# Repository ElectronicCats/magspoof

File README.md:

# MagSpoof By Electronic Cats
  
<a href="https://github.com/ElectronicCats/magspoof/wiki">

<p align=center>

</p>

<p align=center>
Also available at distributors:
</p>
<p align=center>

</p>

# What is MagSpoof?

**MagSpoof by Electronic Cats** is a device that can spoof/emulate any magnetic stripe or credit card. It can work "wirelessly", even on **standard magstripe/credit card readers**, by generating a strong electromagnetic field that emulates a traditional magnetic stripe card.

* Allows you to store all of your credit cards and magstripes in one device
* Works on traditional magstripe readers **wirelessly** (no NFC/RFID required)
* Can **disable** Chip-and-PIN (code not included)
* Correctly **predicts** Amex credit card numbers + expirations from previous card number (code not included)
* Supports all three magnetic stripe tracks, and even supports Track 1+2 simultaneously
* Easy to build using Arduino or other common parts

MagSpoof can be used as a traditional credit card and simply store all of your credit cards (and with modification, can technically disable chip requirements) in various impressive and exciting form factors, or can be used for security research in any area that would traditionally require a magstripe, such as readers for credit cards, drivers licenses, hotel room keys, automated parking lot tickets, etc.

**Note**: The Chip-and-PIN and Amex information is **not** implemented and using MagSpoof requires you to have/own the magstripes that you wish to emulate. Simply having a credit card number and expiration is not enough to perform transactions. MagSpoof **does** allow you to perform research in other areas of magstripes, microcontrollers, and electromagnetism, as well as learn about and create your own devices similar to other existing, commercial technologies such as <a href="http://www.samsung.com/us/support/answer/ANS00043865/997410383/">Samsung MST</a> and <a href="https://onlycoin.com/">Coin</a>.</p>

### ⚠️ Disclaimer ⚠️
MagSpoof is a wireless penetration testing tool intended solely for use in authorized security audits, where such usage is permitted by applicable laws and regulations. Before utilizing this tool, it is crucial to ensure compliance with all relevant legal requirements and obtain appropriate permissions from the relevant authorities.

It is essential to notice that the board does not provide any means or authorization to utilize credit cards or engage in any financial transactions that are not legally authorized. Electronic Cats holds no responsibility for any unauthorized use of the tool or any resulting damages.

-----

# Based in work of Samy Kamkar

**Point of Contact:** [@SamyKamkar](https://twitter.com/samykamkar)

You can see more of my projects at <http://samy.pl> or contact me at <code@samy.pl>.

------

## How to contribute 
 Contributions are welcome! 

Please read the document  [**Contribution Manual**](https://github.com/ElectronicCats/electroniccats-cla/blob/main/electroniccats-contribution-manual.md)  which will show you how to contribute your changes to the project.

✨ Thanks to all our [contributors](https://github.com/ElectronicCats/magspoof/graphs/contributors)! ✨

See  [**_Electronic Cats CLA_**](https://github.com/ElectronicCats/electroniccats-cla/blob/main/electroniccats-cla.md) for more information.

See the [**community code of conduct**](https://github.com/ElectronicCats/electroniccats-cla/blob/main/electroniccats-community-code-of-conduct.md)   for a vision of the community we want to build and what we expect from it.

### Maintainer

Electronic Cats invests time and resources in providing this open-source design design, please support Electronic Cats and open-source hardware by purchasing products from Electronic Cats!

# License

Electronic Cats invests time and resources in providing this open-source design. Please support Electronic Cats and open-source hardware by purchasing products from Electronic Cats!

Designed by Electronic Cats.

Firmware released under an GNU AGPL v3.0 license. See the LICENSE file for more information.

Hardware released under an CERN Open Hardware Licence v1.2. See the LICENSE_HARDWARE file for more information.

Electronic Cats is a registered trademark, please do not use if you sell these PCBs.

30 Octuber 2019

------

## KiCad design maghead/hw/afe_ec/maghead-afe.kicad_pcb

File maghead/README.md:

# MagHead · cabezal lector de banda magnética integrado en PCB (experimento rev A)

Trabajo de investigación y primer experimento fabricable para un sucesor del MagSpoof V5 con lectura y emulación integradas. **Nada de lo que hay aquí se ha construido ni medido todavía**: son cálculos, simulación ideal, diseños de PCB verificados por DRC y software probado con señales sintéticas.

## Recomendación

1. **Ruta principal: cabezal híbrido plano.** Bobinas impresas en la PCB (no en la capa que toca la tarjeta) alrededor de dos ranuras, y una cinta de material magnético blando de 18–50 µm que pasa por las ranuras y forma polos y entrehierro sobre la cara de la PCB. El análisis muestra que dos láminas delgadas coplanares leen igual que un cabezal de anillo del mismo entrehierro; el núcleo no necesita altura. Añade ~0.1 mm al espesor de la placa.
2. **La bobina impresa sin núcleo no sirve como lector de pista 1** (la pista mínima de PCB ya es más ancha que la separación entre transiciones, y equivale a media espira), **pero sí se fabrica como instrumento**: mide el flujo absoluto de la banda y la pérdida por separación, que son las incógnitas que hoy dejan la señal del híbrido con un factor 3 de incertidumbre.
3. **Magnetorresistivos: no en esta tanda.** No hay ningún sensor con distribución establecida cuya geometría esté verificada para 210 bpi; los candidatos solo son plausibles para pista 2 y faltan dos datos del fabricante.
4. **Primero pista 2, después pista 1 con el mismo cabezal** (el cupón se recoloca 3.30 mm con pasadores). Pista 2 valida la cadena; pista 1 decide si la geometría sirve.
5. El riesgo dominante no es el entrehierro ni el ruido, sino **mantener la banda a ≤ 25 µm del polo** con una superficie plana: en pista 1 cada micrómetro cuesta 0.45 dB.

Objetivo mecánico que sale de simular el decodificador: PW50 ≤ ~100 µm en pista 1, es decir separación banda–polo ≲ 35 µm con entrehierro a tope de 25 µm y ≲ 15–20 µm con el de solape.

Números clave (estimaciones, ver `docs/01`): señal del cupón H ≈ 45–250 µV de pico a 19 cm/s (15–50 veces menos que un cabezal comercial), fuente de ≈ 12 Ω, SNR estimada ≥ 26 dB en el peor caso con el frente analógico propuesto.

## Qué se propone fabricar

| Pieza | Qué es |
|---|---|
| `hw/coupon_H` | Cupón híbrido, 4 capas 0.8 mm: 2 sitios × (2 bobinas de 36 espiras en serie-oposición + 2 ranuras). Cinco variantes de ensamblaje sobre la misma PCB |
| `hw/coupon_A` | Cupón de pistas al aire, 2 capas: 3 pistas simples + 1 meandro adaptado a pista 2 |
| `hw/fixture` | Base con lengüetas de presión fresadas y compuertas ópticas, y separador/guía de 1.0 mm. Con el cupón forman el "sándwich" de 2.8 mm |
| `hw/afe` | Frente analógico de 2 canales: esquemático y PCB de 90 × 60 mm, 4 capas |

## Mapa del repositorio

| Ruta | Contenido |
|---|---|
| `docs/01_investigacion_y_calculos.md` | MagSpoof V5 verificado, ISO 7811, física, resultados del modelo, comparación de arquitecturas, fuentes |
| `docs/02_cupones_y_ensamblaje.md` | Geometría, stackup, variantes, procedimiento de ensamblaje, tolerancias, presupuesto de espesor |
| `docs/03_frente_analogico_y_adquisicion.md` | AFE, elección ADC/comparador, placa de desarrollo |
| `docs/04_plan_de_pruebas.md` | Instrumentación, pruebas T0–T10, métricas L1/L2/L3, puertas de decisión |
| `docs/05_incertidumbres_y_pendientes.md` | Parámetros desconocidos, estado de cada entregable, excepciones de DRC, lista previa al pedido |
| `docs/BOM.md` | Fabricantes, números de parte y canales |
| `calc/head_model.py`, `calc/out/` | Modelo: sensibilidad 2D, formas de onda F2F, eficiencia, amplitudes |
| `drawings/` | Secciones y detalle del entrehierro acotados (SVG + PNG, generados por script) |
| `hw/gen_pcbs.py`, `hw/build.sh` | Generador paramétrico de las PCBs, DRC y exportación |
| `hw/*/fab_*`, `hw/*/*_revA_gerbers.zip` | Gerbers y taladros **candidatos**, no liberados |
| `fw/` | Firmware de captura para Pico 2 y decodificador F2F portable en C |
| `tools/` | Síntesis de señal, decodificación, captura, métricas e informes en Python |

## Verificaciones hechas

- KiCad 9.0.9: DRC de las cuatro tarjetas con 0 errores y 0 conexiones pendientes; ERC del AFE con 0 errores y 0 advertencias; PCB del AFE con DRC y paridad de esquemático en 0 errores.
- Comprobación geométrica propia de separación entre espiras (el DRC no la cubre al ser una sola red): mínimo 0.127 mm, 0 violaciones.
- Netlist del AFE contra tabla independiente: coincide.
- Software: 172 pruebas en Python y 125 comprobaciones en C superadas con señales sintéticas; el firmware compila para Pico 2 y Pico con el SDK real, sin probar en placa.
- Solver de campo contra la solución analítica de Karlqvist: 1.5 % en el pico.

## Qué falta para fabricar

La lista completa está en `docs/05`, §4. Lo esencial: revisión humana de los diseños, confirmar capacidades del fabricante de PCB (ranuras de 1.0 mm, 0.127 mm en 4 capas de 0.8 mm), verificar la huella del sensor óptico contra su hoja de datos, tener el material magnético confirmado y elegir el cabezal comercial de referencia.

## Reproducir

```sh
pip install numpy scipy matplotlib cairosvg
python3 calc/head_model.py          # modelo y figuras
python3 drawings/make_drawings.py   # dibujos
sh hw/build.sh                      # PCBs + DRC + Gerbers (usa la imagen Docker kicad/kicad:9.0)
sh hw/afe/build.sh                  # esquemático + ERC + netlist
```

Licencia: la del repositorio (hardware abierto, ver `LICENSE_HARDWARE`).

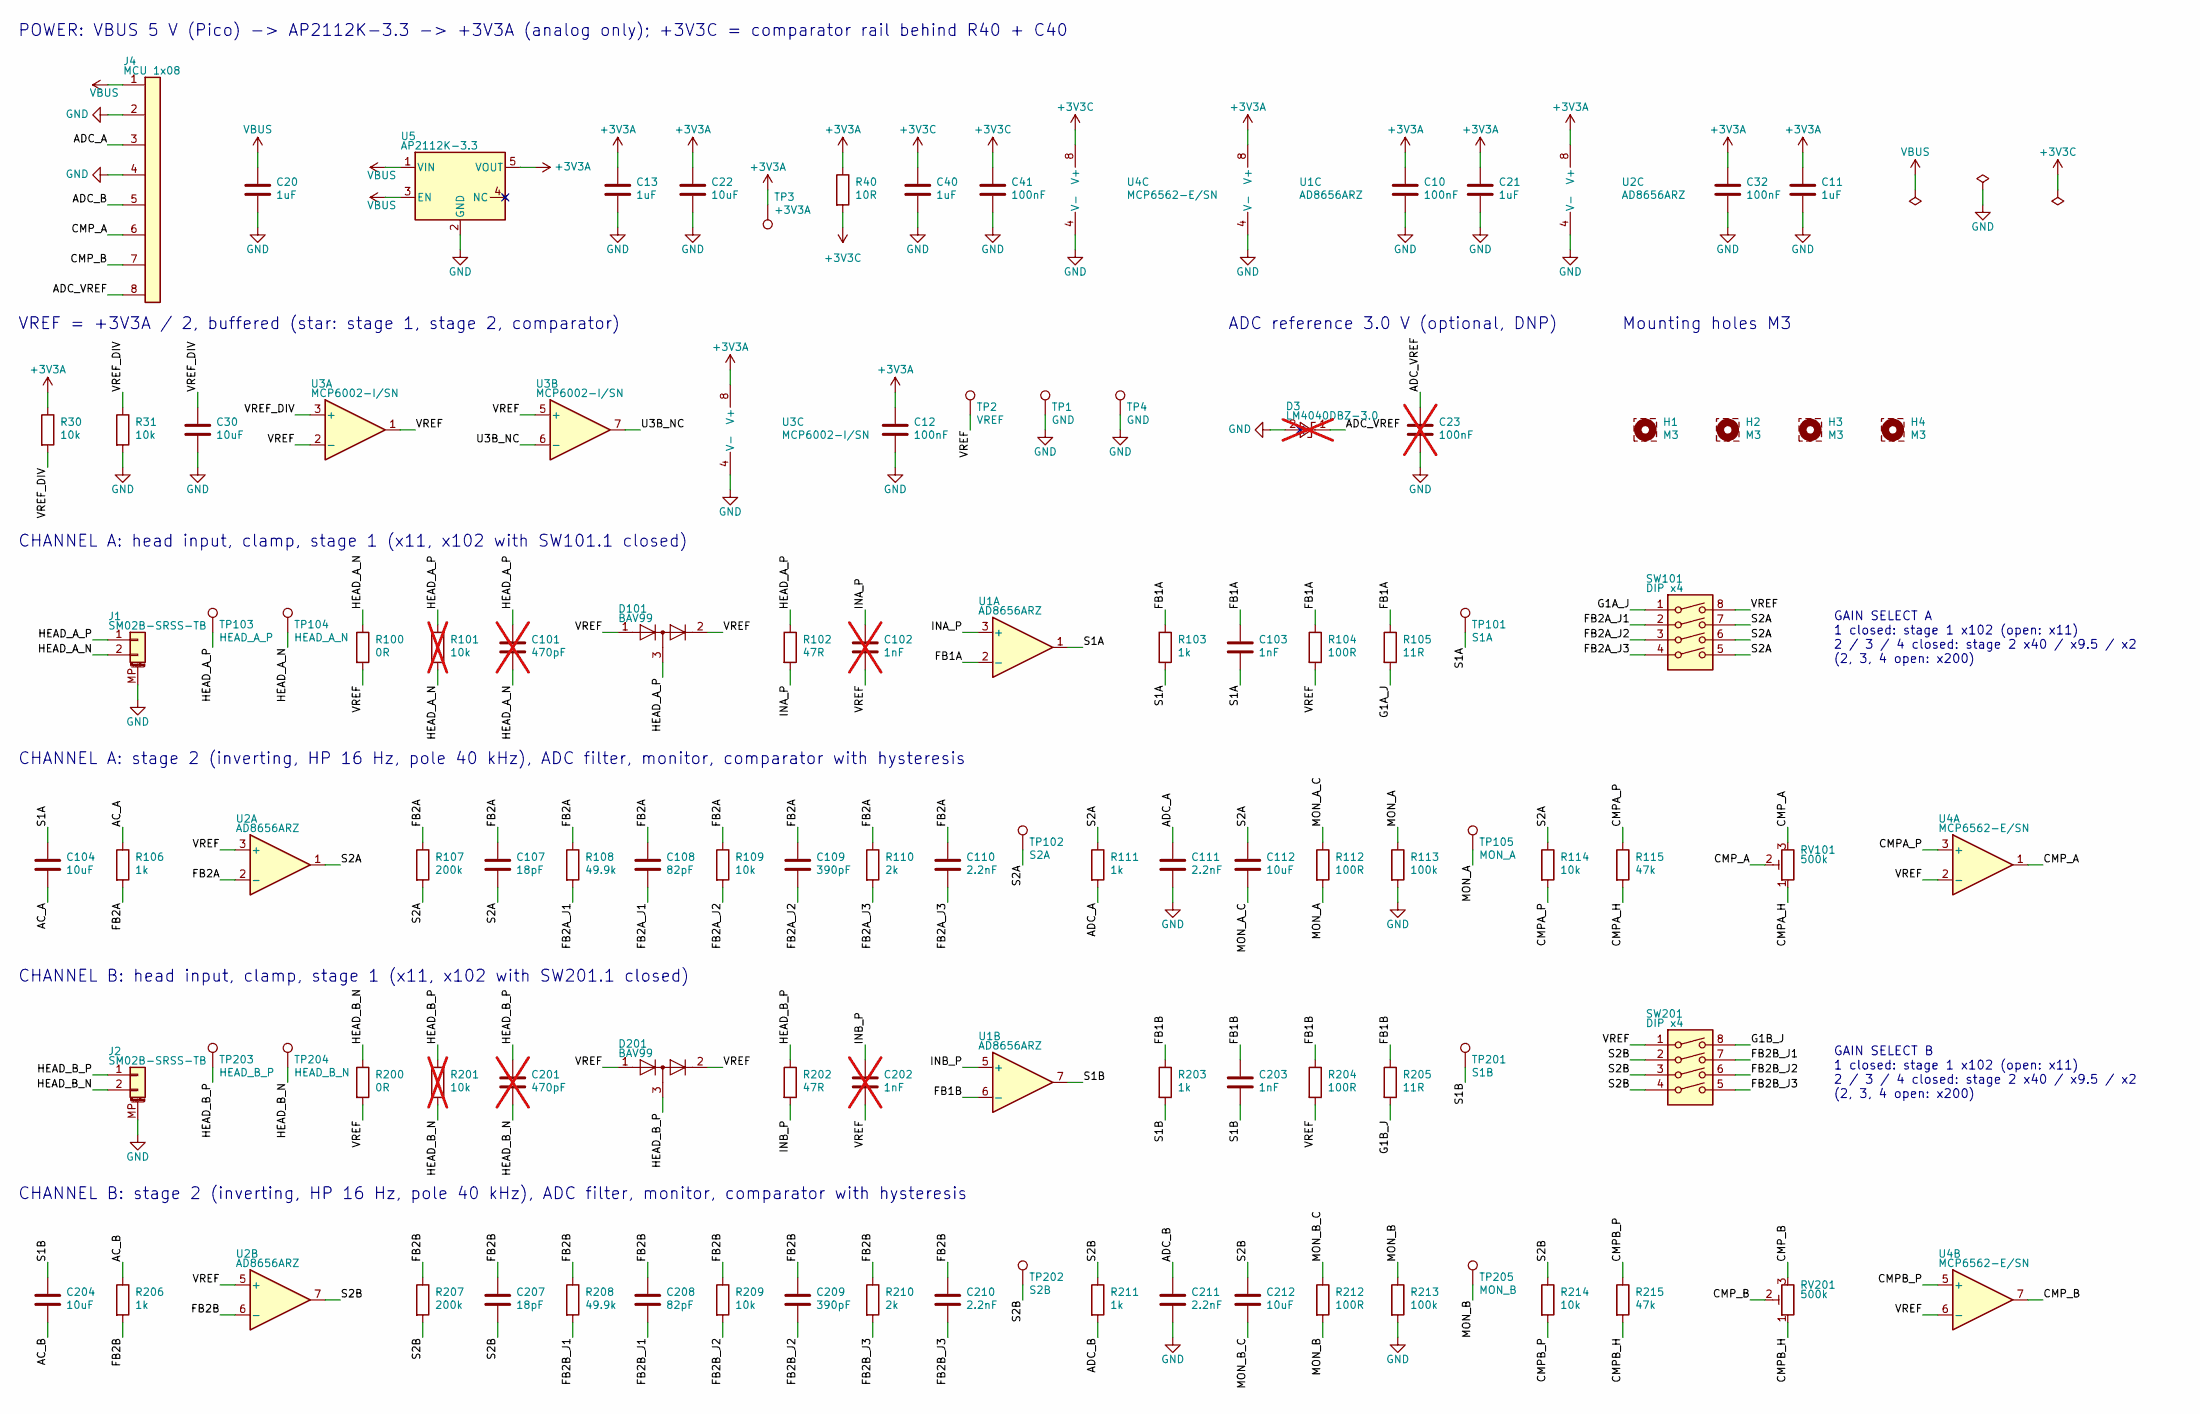
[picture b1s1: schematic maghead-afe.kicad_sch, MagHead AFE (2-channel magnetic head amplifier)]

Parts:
C10, C12, C32, C41: 100nF; C_0603_1608Metric
C11, C13, C20, C21, C40: 1uF; C_0603_1608Metric
C22, C30, C104, C112, C204, C212: 10uF; C_0603_1608Metric
C23: 100nF; C_0603_1608Metric; not fitted
C101, C201: 470pF; C_0603_1608Metric; not fitted
C102, C202: 1nF; C_0603_1608Metric; not fitted
C103, C203: 1nF; C_0603_1608Metric
C107, C207: 18pF; C_0603_1608Metric
C108, C208: 82pF; C_0603_1608Metric
C109, C209: 390pF; C_0603_1608Metric
C110, C111, C210, C211: 2.2nF; C_0603_1608Metric
D3: LM4040DBZ-3.0; SOT-23; not fitted
D101, D201: BAV99; SOT-23
H1, H2, H3, H4: M3; MountingHole_3.2mm_M3
J1, J2: SM02B-SRSS-TB; JST_SH_SM02B-SRSS-TB_1x02-1MP_P1.00mm_Horizontal
J4: MCU 1x08; PinHeader_1x08_P2.54mm_Vertical
R30, R31, R109, R114, R209, R214: 10k; R_0603_1608Metric
R40: 10R; R_0603_1608Metric
R100, R200: 0R; R_0603_1608Metric
R101, R201: 10k; R_0603_1608Metric; not fitted
R102, R202: 47R; R_0603_1608Metric
R103, R106, R111, R203, R206, R211: 1k; R_0603_1608Metric
R104, R112, R204, R212: 100R; R_0603_1608Metric
R105, R205: 11R; R_0603_1608Metric
R107, R207: 200k; R_0603_1608Metric
R108, R208: 49.9k; R_0603_1608Metric
R110, R210: 2k; R_0603_1608Metric
R113, R213: 100k; R_0603_1608Metric
R115, R215: 47k; R_0603_1608Metric
RV101, RV201: 500k; Potentiometer_Bourns_TC33X_Vertical
SW101, SW201: DIP x4; SW_DIP_SPSTx04_Slide_KingTek_DSHP04TS_W7.62mm_P1.27mm
TP1, TP4: GND; TestPoint_Pad_D1.5mm
TP2: VREF; TestPoint_Pad_D1.5mm
TP3: +3V3A; TestPoint_Pad_D1.5mm
TP101: S1A; TestPoint_Pad_D1.5mm
TP102: S2A; TestPoint_Pad_D1.5mm
TP103: HEAD_A_P; TestPoint_Pad_2.0x2.0mm
TP104: HEAD_A_N; TestPoint_Pad_2.0x2.0mm
TP105: MON_A; TestPoint_Pad_D1.5mm
TP201: S1B; TestPoint_Pad_D1.5mm
TP202: S2B; TestPoint_Pad_D1.5mm
TP203: HEAD_B_P; TestPoint_Pad_2.0x2.0mm
TP204: HEAD_B_N; TestPoint_Pad_2.0x2.0mm
TP205: MON_B; TestPoint_Pad_D1.5mm
U1, U2: AD8656ARZ; SOIC-8_3.9x4.9mm_P1.27mm
U3: MCP6002-I/SN; SOIC-8_3.9x4.9mm_P1.27mm
U4: MCP6562-E/SN; SOIC-8_3.9x4.9mm_P1.27mm
U5: AP2112K-3.3; SOT-23-5; LCSC# C47773

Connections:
+3V3A: C10.1, C11.1, C12.1, C13.1, C21.1, C22.1, C32.1, R30.1, R40.1, TP3.1, U1.8 (V+), U2.8 (V+), U3.8 (V+), U5.5 (VOUT)
+3V3C: C40.1, C41.1, R40.2, U4.8 (V+)
/AC_A: C104.2, R106.1
/AC_B: C204.2, R206.1
/ADC_A: C111.1, J4.3, R111.2
/ADC_B: C211.1, J4.5, R211.2
/ADC_VREF: C23.1, D3.1 (K), J4.8
/CMPA_H: R115.2, RV101.1
/CMPA_P: R114.2, R115.1, U4.3 (+)
/CMPB_H: R215.2, RV201.1
/CMPB_P: R214.2, R215.1, U4.5 (+)
/CMP_A: J4.6, RV101.2, RV101.3, U4.1
/CMP_B: J4.7, RV201.2, RV201.3, U4.7
/FB1A: C103.1, R103.1, R104.1, R105.1, U1.2 (-)
/FB1B: C203.1, R203.1, R204.1, R205.1, U1.6 (-)
/FB2A: C107.1, C108.1, C109.1, C110.1, R106.2, R107.1, R108.1, R109.1, R110.1, U2.2 (-)
/FB2A_J1: C108.2, R108.2, SW101.2
/FB2A_J2: C109.2, R109.2, SW101.3
/FB2A_J3: C110.2, R110.2, SW101.4
/FB2B: C207.1, C208.1, C209.1, C210.1, R206.2, R207.1, R208.1, R209.1, R210.1, U2.6 (-)
/FB2B_J1: C208.2, R208.2, SW201.7
/FB2B_J2: C209.2, R209.2, SW201.6
/FB2B_J3: C210.2, R210.2, SW201.5
/G1A_J: R105.2, SW101.1
/G1B_J: R205.2, SW201.8
/HEAD_A_N: C101.2, J1.2, R100.1, R101.2, TP104.1
/HEAD_A_P: C101.1, D101.3 (K), J1.1, R101.1, R102.1, TP103.1
/HEAD_B_N: C201.2, J2.2, R200.1, R201.2, TP204.1
/HEAD_B_P: C201.1, D201.3 (K), J2.1, R201.1, R202.1, TP203.1
/INA_P: C102.1, R102.2, U1.3 (+)
/INB_P: C202.1, R202.2, U1.5 (+)
/MON_A: R112.2, R113.1, TP105.1
/MON_A_C: C112.2, R112.1
/MON_B: R212.2, R213.1, TP205.1
/MON_B_C: C212.2, R212.1
/S1A: C103.2, C104.1, R103.2, TP101.1, U1.1
/S1B: C203.2, C204.1, R203.2, TP201.1, U1.7
/S2A: C107.2, C112.1, R107.2, R111.1, R114.1, SW101.5, SW101.6, SW101.7, TP102.1, U2.1
/S2B: C207.2, C212.1, R207.2, R211.1, R214.1, SW201.2, SW201.3, SW201.4, TP202.1, U2.7
/U3B_NC: U3.6 (-), U3.7
/VREF: C102.2, C202.2, D101.1 (K), D101.2 (A), D201.1 (K), D201.2 (A), R100.2, R104.2, R200.2, R204.2, SW101.8, SW201.1, TP2.1, U2.3 (+), U2.5 (+), U3.1, U3.2 (-), U3.5 (+), U4.2 (-), U4.6 (-)
/VREF_DIV: C30.1, R30.2, R31.1, U3.3 (+)
GND: C10.2, C11.2, C12.2, C13.2, C20.2, C21.2, C22.2, C23.2, C30.2, C32.2, C40.2, C41.2, C111.2, C211.2, D3.2 (A), J1.MP (MountPin), J2.MP (MountPin), J4.2, J4.4, R31.2, R113.2, R213.2, TP1.1, TP4.1, U1.4 (V-), U2.4 (V-), U3.4 (V-), U4.4 (V-), U5.2 (GND)
VBUS: C20.1, J4.1, U5.1 (VIN), U5.3 (EN)

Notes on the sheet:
POWER: VBUS 5 V (Pico) -> AP2112K-3.3 -> +3V3A (analog only); +3V3C = comparator rail behind R40 + C40
VREF = +3V3A / 2, buffered (star: stage 1, stage 2, comparator)
ADC reference 3.0 V (optional, DNP)
Mounting holes M3
CHANNEL A: head input, clamp, stage 1 (x11, x102 with SW101.1 closed)
GAIN SELECT A 1 closed: stage 1 x102 (open: x11) 2 / 3 / 4 closed: stage 2 x40 / x9.5 / x2 (2, 3, 4 open: x200)
CHANNEL A: stage 2 (inverting, HP 16 Hz, pole 40 kHz), ADC filter, monitor, comparator with hysteresis
CHANNEL B: head input, clamp, stage 1 (x11, x102 with SW201.1 closed)
GAIN SELECT B 1 closed: stage 1 x102 (open: x11) 2 / 3 / 4 closed: stage 2 x40 / x9.5 / x2 (2, 3, 4 open: x200)
CHANNEL B: stage 2 (inverting, HP 16 Hz, pole 40 kHz), ADC filter, monitor, comparator with hysteresis

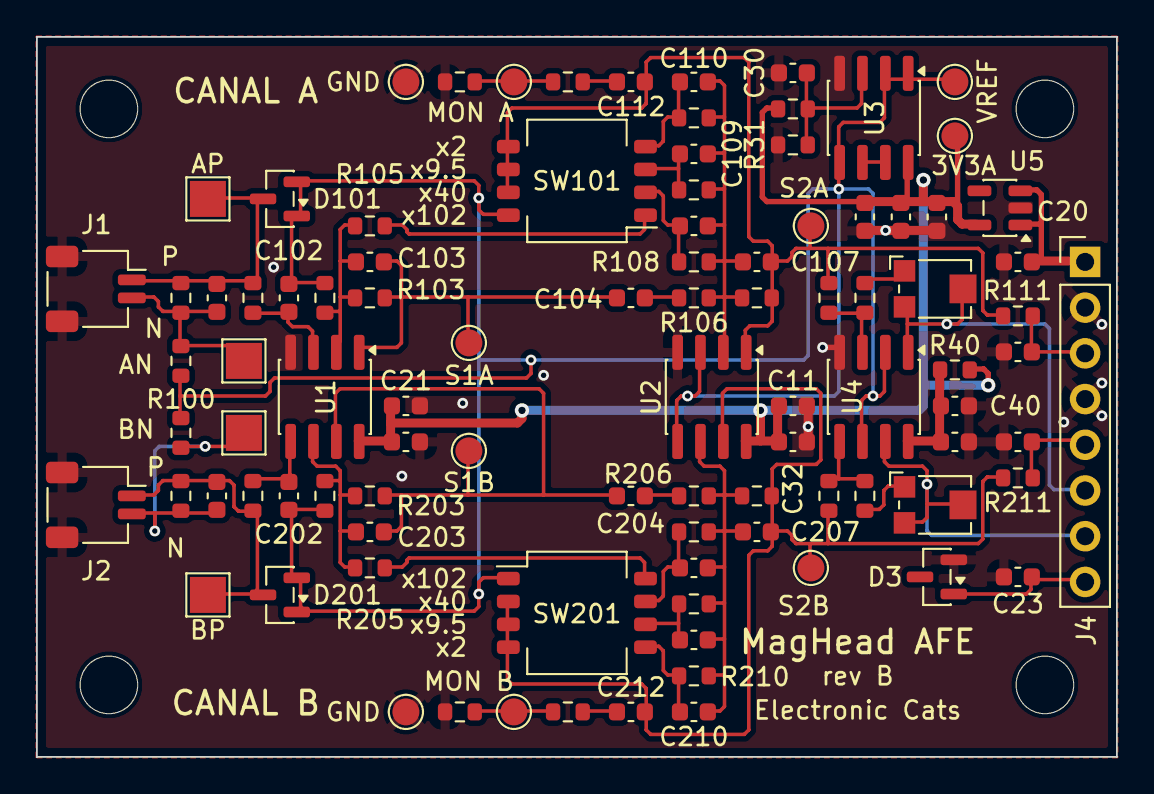
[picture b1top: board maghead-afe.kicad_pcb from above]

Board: 2 copper layers, 60.0 x 40.0 mm, 100 parts (0 on the bottom side), 44 nets.

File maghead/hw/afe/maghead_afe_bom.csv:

"Refs","Valor","Huella","MPN","Fabricante","Cant","DNP"
"C10,C12,C32,C41","100nF","Capacitor_SMD:C_0603_1608Metric","CL10B104KB8NNNC","Samsung Electro-Mechanics","4",""
"C11,C13,C20,C21,C40","1uF","Capacitor_SMD:C_0603_1608Metric","CL10B105KA8NNNC","Samsung Electro-Mechanics","5",""
"C22,C30,C104,C112,C204,C212","10uF","Capacitor_SMD:C_0805_2012Metric","CL21A106KOQNNNE","Samsung Electro-Mechanics","6",""
"C23","100nF","Capacitor_SMD:C_0603_1608Metric","CL10B104KB8NNNC","Samsung Electro-Mechanics","1","DNP"
"C101,C201","470pF","Capacitor_SMD:C_0603_1608Metric","CL10C471JB8NNNC","Samsung Electro-Mechanics","2","DNP"
"C102,C202","1nF","Capacitor_SMD:C_0603_1608Metric","CL10C102JB8NNNC","Samsung Electro-Mechanics","2","DNP"
"C103,C203","1nF","Capacitor_SMD:C_0603_1608Metric","CL10C102JB8NNNC","Samsung Electro-Mechanics","2",""
"C107,C207","18pF","Capacitor_SMD:C_0603_1608Metric","CL10C180JB8NNNC","Samsung Electro-Mechanics","2",""
"C108,C208","82pF","Capacitor_SMD:C_0603_1608Metric","CL10C820JB8NNNC","Samsung Electro-Mechanics","2",""
"C109,C209","390pF","Capacitor_SMD:C_0603_1608Metric","CL10C391JB8NNNC","Samsung Electro-Mechanics","2",""
"C110,C111,C210,C211","2.2nF","Capacitor_SMD:C_0603_1608Metric","CL10C222JB8NNNC","Samsung Electro-Mechanics","4",""
"D3","LM4040DBZ-3.0","Package_TO_SOT_SMD:SOT-23","LM4040C30IDBZR","Texas Instruments","1","DNP"
"D101,D201","BAV99","Package_TO_SOT_SMD:SOT-23","BAV99,215","Nexperia","2",""
"J1","CABEZAL A","Connector_PinHeader_2.54mm:PinHeader_1x03_P2.54mm_Vertical","61300311121","Wurth Elektronik","1",""
"J2","CABEZAL B","Connector_PinHeader_2.54mm:PinHeader_1x03_P2.54mm_Vertical","61300311121","Wurth Elektronik","1",""
"J3","Jack 3.5 mm MONITOR","Connector_Audio:Jack_3.5mm_CUI_SJ1-3523N_Horizontal","SJ1-3523N","CUI Devices","1",""
"J4","MCU 1x08","Connector_PinHeader_2.54mm:PinHeader_1x08_P2.54mm_Vertical","61300811121","Wurth Elektronik","1",""
"JP101,JP102,JP103,JP104,JP201,JP202,JP203,JP204","Jumper 1x02","Connector_PinHeader_2.54mm:PinHeader_1x02_P2.54mm_Vertical","61300211121","Wurth Elektronik","8",""
"R30,R31,R109,R114,R209,R214","10k","Resistor_SMD:R_0603_1608Metric","RC0603FR-0710KL","Yageo","6",""
"R40","10R","Resistor_SMD:R_0603_1608Metric","RC0603FR-0710RL","Yageo","1",""
"R100,R200","0R","Resistor_SMD:R_0603_1608Metric","RC0603JR-070RL","Yageo","2",""
"R101,R201","10k","Resistor_SMD:R_0603_1608Metric","RC0603FR-0710KL","Yageo","2","DNP"
"R102,R202","47R","Resistor_SMD:R_0603_1608Metric","RC0603FR-0747RL","Yageo","2",""
"R103,R106,R111,R203,R206,R211","1k","Resistor_SMD:R_0603_1608Metric","RC0603FR-071KL","Yageo","6",""
"R104,R112,R204,R212","100R","Resistor_SMD:R_0603_1608Metric","RC0603FR-07100RL","Yageo","4",""
"R105,R205","11R","Resistor_SMD:R_0603_1608Metric","RC0603FR-0711RL","Yageo","2",""
"R107,R207","200k","Resistor_SMD:R_0603_1608Metric","RC0603FR-07200KL","Yageo","2",""
"R108,R208","49.9k","Resistor_SMD:R_0603_1608Metric","RC0603FR-0749K9L","Yageo","2",""
"R110,R210","2k","Resistor_SMD:R_0603_1608Metric","RC0603FR-072KL","Yageo","2",""
"R113,R213","100k","Resistor_SMD:R_0603_1608Metric","RC0603FR-07100KL","Yageo","2",""
"R115,R215","47k","Resistor_SMD:R_0603_1608Metric","RC0603FR-0747KL","Yageo","2",""
"RV101,RV201","500k","Potentiometer_THT:Potentiometer_Bourns_3296W_Vertical","3296W-1-504LF","Bourns","2",""
"TP1","TP GND","TestPoint:TestPoint_Keystone_5019_Miniature","5019","Keystone Electronics","1",""
"TP2","TP VREF","TestPoint:TestPoint_Keystone_5019_Miniature","5019","Keystone Electronics","1",""
"TP3","TP +3V3A","TestPoint:TestPoint_Keystone_5019_Miniature","5019","Keystone Electronics","1",""
"TP101","TP S1A","TestPoint:TestPoint_Keystone_5019_Miniature","5019","Keystone Electronics","1",""
"TP102","TP S2A","TestPoint:TestPoint_Keystone_5019_Miniature","5019","Keystone Electronics","1",""
"TP201","TP S1B","TestPoint:TestPoint_Keystone_5019_Miniature","5019","Keystone Electronics","1",""
"TP202","TP S2B","TestPoint:TestPoint_Keystone_5019_Miniature","5019","Keystone Electronics","1",""
"U1,U2","AD8656ARZ","Package_SO:SOIC-8_3.9x4.9mm_P1.27mm","AD8656ARZ","Analog Devices","2",""
"U3","MCP6002-I/SN","Package_SO:SOIC-8_3.9x4.9mm_P1.27mm","MCP6002-I/SN","Microchip","1",""
"U4","MCP6562-E/SN","Package_SO:SOIC-8_3.9x4.9mm_P1.27mm","MCP6562-E/SN","Microchip","1",""
"U5","AP2112K-3.3","Package_TO_SOT_SMD:SOT-23-5","AP2112K-3.3TRG1","Diodes Incorporated","1",""

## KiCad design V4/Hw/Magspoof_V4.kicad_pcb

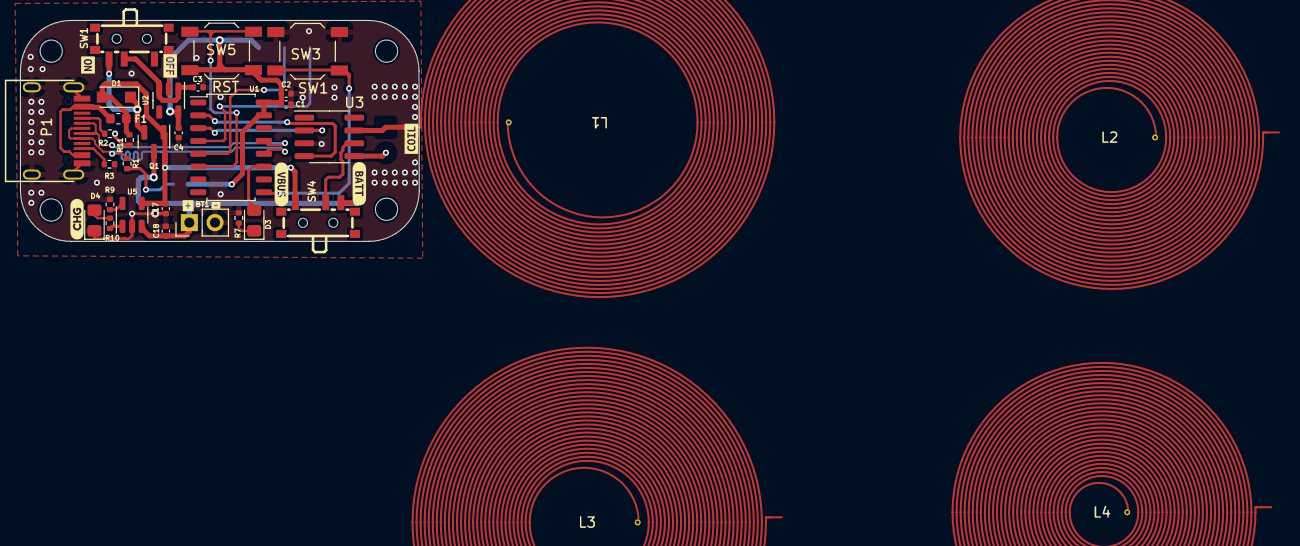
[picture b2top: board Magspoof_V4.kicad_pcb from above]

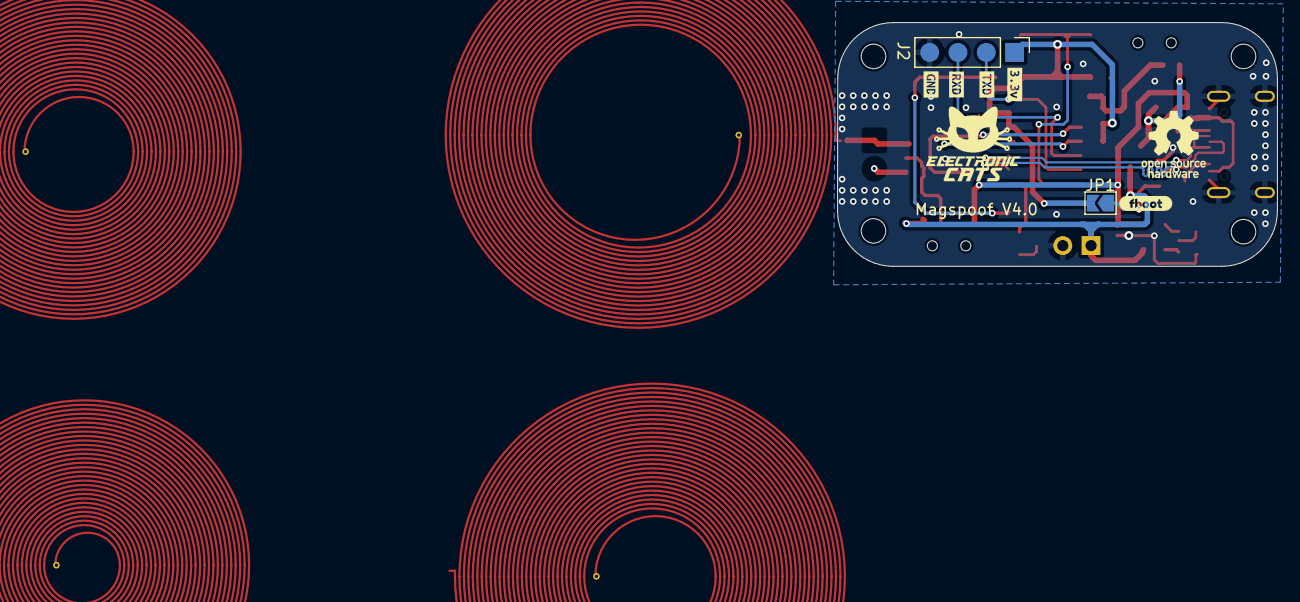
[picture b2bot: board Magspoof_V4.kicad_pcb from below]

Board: 2 copper layers, 39.5 x 21.9 mm, 51 parts (7 on the bottom side), 25 nets.

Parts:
BT1: Battery_Cell; PinHeader_1x02_P2.54mm_Vertical
C1, C2: 0.1uF; C_0402_1005Metric
C3, C4, C17, C18: 10uF; C_0402_1005Metric
D1: MBR120; D_SOD-123F
D3: Status; LED_0805_2012Metric_Pad1.15x1.40mm_HandSolder
D4: CHG; LED_0805_2012Metric_Pad1.15x1.40mm_HandSolder
F1: 0.5A; Fuse_0603_1608Metric
H1, H2, H3, H4: MountingHole; MountingHole_2.2mm_M2
J2: SWD; PinHeader_1x04_P2.54mm_Vertical
JP1: boot; SolderJumper-2_P1.3mm_Open_TrianglePad1.0x1.5mm
L1: 20t_35mm; Coil_20t_35mm_0.2_0.2_0.6_0.3
L2: 25t_30mm; Coil_25t_30mm_0.2_0.2_0.6_0.3
L3: 30t_35mm; Coil_30t_35mm_0.2_0.2_0.6_0.3
L4: 30t_30mm; Coil_30t_30mm_0.2_0.2_0.6_0.3
P1: USB_C_Plug_USB2.0; C393939
Q1: DMG3415U-7; SOT-23
R1: 20K; R_0402_1005Metric
R2, R3, R9: 5.1k; R_0402_1005Metric
R7: 180R; R_0402_1005Metric
R10: 470; R_0402_1005Metric
R11: 100K; R_0402_1005Metric
SW1: ON; SW-SMD_SSSS811101
SW3: S1; SW_SPST_TL3342
SW4: SOURCE MAG; SW-SMD_SSSS811101
SW5: RESET; SW_SPST_TL3342
U1: CH552G; SOP-16_4.55x10.3mm_P1.27mm
U2: AP2112K-3.3; SOT-23-5
U3: TC4424; SOIC-8_3.9x4.9mm_P1.27mm
U5: MCP73831; SOT-23-5
kibuzzard-6435F1C7: G***; kibuzzard-6435F1C7
kibuzzard-6435F3C4: G***; kibuzzard-6435F3C4
kibuzzard-6435F22E: G***; kibuzzard-6435F22E
kibuzzard-6436E8D1: G***; kibuzzard-6436E8D1
kibuzzard-6436E8D8: G***; kibuzzard-6436E8D8
kibuzzard-6436EA37: G***; kibuzzard-6436EA37
kibuzzard-6436EA46: G***; kibuzzard-6436EA46
kibuzzard-6436EF9F: G***; kibuzzard-6436EF9F
kibuzzard-6436EF98: G***; kibuzzard-6436EF98
kibuzzard-64629FC5: G***; kibuzzard-64629FC5
kibuzzard-64629FDC: G***; kibuzzard-64629FDC
kibuzzard-64665C6A: G***; kibuzzard-64665C6A
kibuzzard-64665C9F: G***; kibuzzard-64665C9F

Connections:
+3V3: C1.1, C2.1, C4.1, J2.1, JP1.2 (B), SW5.2, U1.15 (VCC), U1.16 (V33), U2.5 (VOUT)
+BATT: BT1.1 (+), C18.1, Q1.3 (D), SW4.3 (C), U5.3 (VBAT)
/D+: P1.A6 (D+), R1.2, U1.12 (P3.6)
/D-: P1.A7 (D-), U1.13 (P3.7)
/IN_A: U1.2 (P1.4), U3.4 (IN_B)
/IN_B: U1.3 (P1.5), U3.2 (IN_A)
/LED: D3.2 (A), U1.11 (P3.4)
/Out_A: L1.1, L2.1, L3.1, L4.1, U3.7 (OUT_A)
/RST: SW5.1, U1.6 (RST)
/RXD: J2.3, U1.4 (P1.6)
/SW1: SW3.2, U1.9 (P1.1)
/TXD: J2.2, U1.5 (P1.7)
GND: BT1.2 (-), C1.2, C2.2, C3.2, C4.2, C17.2, C18.2, D4.1 (K), J2.4, P1.A1 (GND), P1.S1 (SHIELD), R2.1, R3.1, R7.2, R9.2, R11.2, SW3.1, U1.14 (GND), U2.2 (GND), U3.3 (GND), U5.2 (VSS)
unnamed: D1.1 (K), Q1.2 (S), SW1.3 (A)
unnamed: D3.1 (K), R7.1
unnamed: D4.2 (A), R10.2
unnamed: F1.1, P1.A4 (VBUS)
unnamed: JP1.1 (A), R1.1
unnamed: P1.A5 (CC), R2.2
unnamed: P1.B5 (VCONN), R3.2
unnamed: C3.1, SW1.2 (B), U2.1 (VIN), U2.3 (EN)
unnamed: SW4.2 (B), U3.6 (VDD)
unnamed: R9.1, U5.5 (PROG)
unnamed: R10.1, U5.1 (STAT)
VBUS: C17.1, D1.2 (A), F1.2, Q1.1 (G), R11.1, SW4.1 (A), U5.4 (VDD)

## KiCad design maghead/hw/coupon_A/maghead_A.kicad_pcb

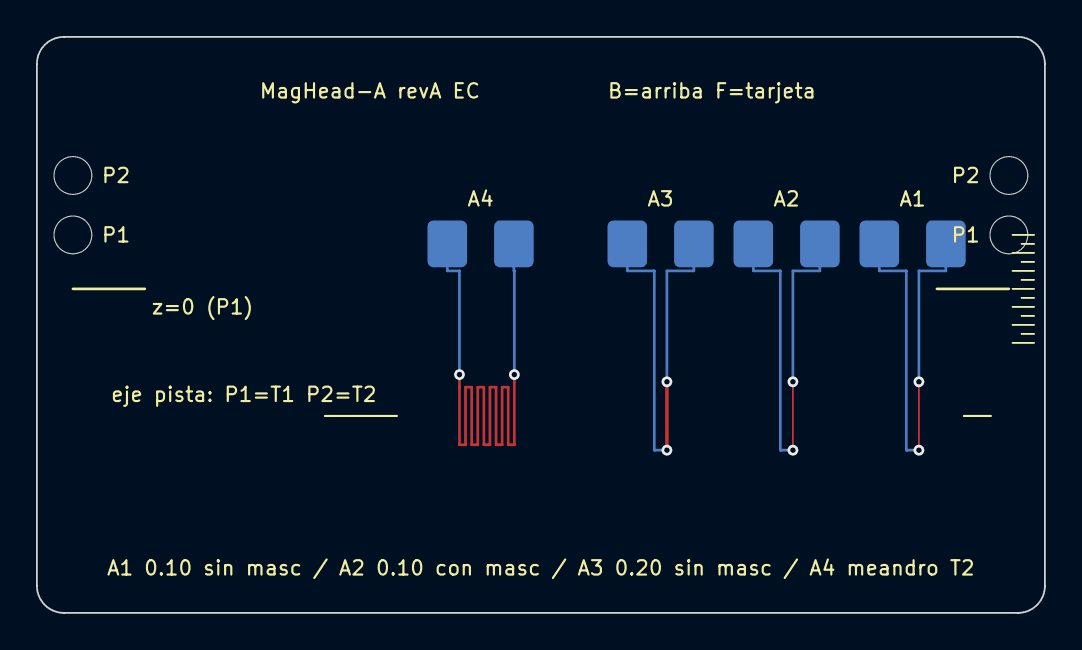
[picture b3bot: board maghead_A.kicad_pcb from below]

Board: 2 copper layers, 56.0 x 32.0 mm, 15 parts (8 on the bottom side), 4 nets.

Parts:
JA1A, JA1B, JA2A, JA2B, JA3A, JA3B, JA4A, JA4B: WirePad
M3, M3#2, M3#3: NPTH
P1, P1#2, P2, P2#2: NPTH

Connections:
AIR_A1: JA1A.1, JA1B.1
AIR_A2: JA2A.1, JA2B.1
AIR_A3: JA3A.1, JA3B.1
AIR_A4: JA4A.1, JA4B.1

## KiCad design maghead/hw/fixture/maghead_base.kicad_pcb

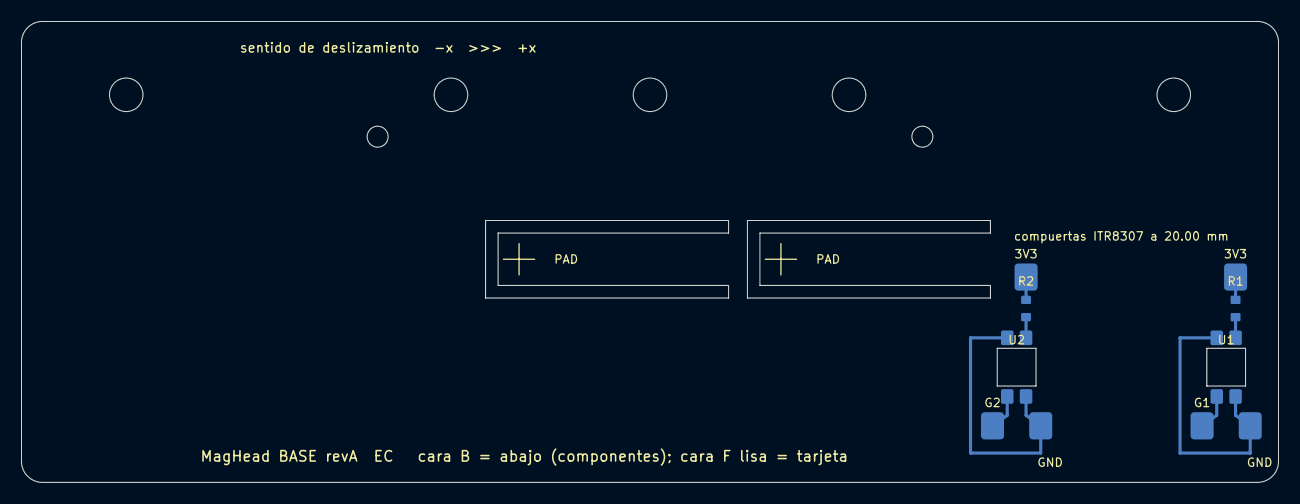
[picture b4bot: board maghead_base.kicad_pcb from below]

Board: 2 copper layers, 120.0 x 44.0 mm, 17 parts (10 on the bottom side), 8 nets.

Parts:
DW: NPTH
DW#2: NPTH
JC1, JC2: WirePad
JK1, JK2: WirePad
JV1, JV2: WirePad
M3, M3#2, M3#3, M3#4, M3#5: NPTH
R1, R2: R_0603_150R
U1, U2: ITR8307_Reverse

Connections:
GATE1: JC1.1, U1.3
GATE2: JC2.1, U2.3
GND1: JK1.1, U1.1, U1.4
GND2: JK2.1, U2.1, U2.4
LED1_A: R1.2, U1.2
LED2_A: R2.2, U2.2
V1: JV1.1, R1.1
V2: JV2.1, R2.1

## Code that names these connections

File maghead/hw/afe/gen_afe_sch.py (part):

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               value="LM4040DBZ-3.0", mpn="LM4040C30IDBZR", mfr="Texas Instruments", dnp=True)
    d3.fields(ref=(3.0, -1.2, "l"), val=(3.0, 1.2, "l"))
    wire(L(42, y), L(58, y))
    label("ADC_VREF", L(42, y))
    wire(d3.pin(2), L(48, y + 4))
    power("GND", L(48, y + 4))
    Cgnd("C23", "100nF", ox + 58, oy + y, dnp=True)
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    power("GND", r31.pin(2))
    ua = opamp("U3", 1, ox + 23, oy + 13)
    wire(L(6, 12), ua.plus)
    label("VREF_DIV", L(14, 12))
    Cgnd("C30", "10uF", ox + 12, oy + 12)
    wire(ua.minus, L(19, 14), L(19, 17), L(28, 17), L(28, 13))
    wire(ua.out, L(34, 13))
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    label("VREF", L(17, 24), 180)
    wire(ub.minus, L(19, 26), L(19, 29), L(28, 29), L(28, 25))
    wire(ub.out, L(31, 25))
    label("U3B_NC", L(31, 25))
    text("U3B sin uso: seguidor\nde VREF, salida al aire.", ox + 29.5, oy + 26.5)
    text("Sin condensador en VREF\n(evitar carga capacitiva).", ox + 29.5, oy + 15)

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    j3 = place("J3", "Connector_Audio:AudioJack3", ox + 31, oy + 12, value="Jack 3.5 mm MONITOR",
               fp="Connector_Audio:Jack_3.5mm_CUI_SJ1-3523N_Horizontal", mpn="SJ1-3523N", mfr="CUI Devices")
    j3.fields(ref=(0, -8.9, "c"), val=(0, -6.4, "c"))
    wire(j3.pin("T"), L(36, 13)); label("MON_A", L(36, 13))
    wire(j3.pin("R"), L(36, 12)); label("MON_B", L(36, 12))
    wire(j3.pin("S"), L(42, 11), L(42, 15))
    power("GND", L(42, 15))
    text("Punta = MON_A, anillo = MON_B,\nmanga = GND.", ox + 27, oy + 16)
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
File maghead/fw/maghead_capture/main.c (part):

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
#define FW_VERSION "maghead_capture 0.1.0"

#define PIN_ADC_A   26
#define PIN_ADC_B   27
#define PIN_DIG0    2      /* GP2..GP5 consecutivos */
#define PIN_GATE1   4
#define PIN_GATE2   5
#ifdef PICO_DEFAULT_LED_PIN
#define PIN_LED     PICO_DEFAULT_LED_PIN
#else
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    if (w - evq_r < EVQ_LEN) {
        gate_ev_t *e = &evq[w % EVQ_LEN];
        e->t_us = time_us_64();
        e->src = (gpio == PIN_GATE1) ? 1 : 2;
        e->level = gpio_get(gpio) ? 0 : 1;        /* activa a nivel bajo: 1 = tarjeta presente */
        evq_w = w + 1;
    }
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        gpio_init(PIN_DIG0 + i);
        gpio_set_dir(PIN_DIG0 + i, GPIO_IN);
    }
    gpio_pull_up(PIN_GATE1);                        /* barreras de colector abierto */
    gpio_pull_up(PIN_GATE2);
    gpio_set_irq_enabled_with_callback(PIN_GATE1, GPIO_IRQ_EDGE_RISE | GPIO_IRQ_EDGE_FALL, true, &gate_irq);
    gpio_set_irq_enabled(PIN_GATE2, GPIO_IRQ_EDGE_RISE | GPIO_IRQ_EDGE_FALL, true);

    adc_init();
    adc_gpio_init(PIN_ADC_A);
    adc_gpio_init(PIN_ADC_B);

    dig_sm = (uint)pio_claim_unused_sm(dig_pio, true);
    dig_offset = (uint)pio_add_program(dig_pio, &dig_sample_program);
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
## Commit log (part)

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2023-12-19 Update README.md
    Pictures removed
2023-12-20 Update README.md
    Changes:
    1.- Adding pictures of the device to the presentation and wiki section
    2.- Adding pictures with links to the store and wiki
2023-12-20 Update README.md
    Changes:
    1.- Adding pictures of the device to the general description and wiki section.
    2.- Adding links to the store and the wiki
    3.- Adding picture for the license
2023-12-21 Update README.md
    Changes in the button to the store
2023-12-26 Update README.md
    Rearrange of pictures with links to the store and wiki
2024-01-09 Add_Step_File
2024-03-05 feat: flat spiral coil proposals for PCB antenna
2024-03-06 chore: update .gitignore
2024-03-06 feat(hw): add library
2024-03-11 feat(hw): add 2 additional coils and the specs of the coils
2024-03-20 feat(hw): add Test coils panel
2024-03-20 fix(hw): route correction
2024-03-20 feat(hw): panelizing
2024-03-21 fix(hw): change edge cuts
2024-03-21 fix(hw): update edge cuts
2024-03-22 fix(hw): panelization changes
2024-04-04 feat(hw): Magspoof V5 pcb and layaout added
2024-04-05 Create LICENSE_HARDWARE
2024-04-08 feat(hw): components got reorganized
2024-04-08 feat(hw): TX and RX pins updated
2024-04-08 feat(hw): path width changed
2024-04-09 feat (docs): Update README.md
    How to contribute added
2024-04-09 fix(hw): Some paths got corrections
2024-04-09 fix(hw): pins Serial boot
2024-04-09 feat(hw): add logos
2024-04-10 feat(hw): added TX and RX Boot pins
2024-04-10 feat(hw): logos
2024-04-11 feat(hw): components organization updated
2024-04-11 feat(hw): BOM generated
2024-04-11 fix(hw): orientation logo
2024-04-11 feat(hw): move label batt
2024-04-11 feat(hw): BOM got updated
2024-04-11 feat(hw): USB manufacture part updated
2024-04-11 fix(hw): layer correction of dimension comments
2024-04-24 feat(docs): add distributor button
2024-04-24 feat(docs): add text and distributor button
2024-05-02 feat: testing firmware added
2024-05-09 chore: added comments
2024-05-13 feat: added serialComplete var
2024-05-15 feat: add path for firmware
2024-05-16 feat: added help menu
2024-06-26 fix(hw): DNP update of the list components
2024-07-01 fix(hw): change path test coils
2024-07-01 fix: remove code comments
2024-07-02 fix: NL and CR ok
2024-07-02 feat: add showEEPROM()
2024-07-15 feat: load contents from EEPROM
2024-07-16 fix: typo name
2024-07-23 feat (docs): Update README.md
    Updated to Magspoof V5.
2024-07-25 feat (docs): Update README.md
2024-07-30 feat: update example allinone v4
2024-10-28 Fix: typo
2025-04-02 feat(hw); add STL case files
